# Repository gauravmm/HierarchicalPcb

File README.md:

This project is retired, and has been superseded by [ProjectInstances](https://github.com/OfficialDyray/ProjectInstances/). Please use that instead!

# ~HierarchicalPcb~

This provides a true hierarchical PCB layout engine in KiCad, mirroring its hierarchical schematic capabilities.

Instead of laying out everything in your final file, you can define a sub-PCB next to your sub-schematic file, and HierarchicalPCB will automatically force the sub-PCB to be laid out exactly like that in the final PCB. There's no depth limitation to the nesting -- in fact, we encourage organizing your PCB layouts for maximum reusability.

This is inspired by the venerable [`ReplicateLayout`](https://github.com/MitjaNemec/ReplicateLayout) plugin, and is intended to be a more modular, powerful, and flexible replacement.

**Installation**:

This requires KiCad 8 to run. For now, you have to manually download or clone this repository to the plugin directory. On Windows, this is `C:\Users\<Username>\Documents\KiCad\8.0\3rdparty\plugins`.

I'm working on getting this deployed to the official repository or on hosting my own.

## How To Use

In summary:

1. Organize your schematic into hierarchical sheets, as you would normally do.
2. Create a `.kicad_pcb` file next to a hierarchical sheet and set up the placement of the sub-PCB there.

   a. You should create a project file to help with the placement.
   b. Any footprints missing from the sub-PCB (but present in the schematic) will be ignored during automatic placement.
   c. Any footprints present in the sub-PCB but missing from the main PCB will be ignored.
   d. Any footprints placed off to the left or above the origin will be ignored during automatic placement.

3. Open the main PCB and run the plugin.
4. Select which hierarchical sheets you want to enforce the layout of, and configure which footprint to use as the anchor for each sub-PCB.
5. Click OK and watch the magic happen.

If you wish to see a project that uses this, check out [AngloDox, my keyboard project](https://github.com/gauravmm/AngloDox/). We use HierarchicalPCB to provide for rich per-key circuitry.

### In Detail

Begin by preparing your hierarchical schematic as per normal. In this example, we have a simple circuit for a single key in a keyboard, including an LED and an RC debouncing circuit:

This would be an absolute nightmare to layout ~90 different times; that's where HierarchicalPCB comes in: after creating the schematic inside the main project, we:

1. create a new project with the same name as the `sch` file,
2. open that project in KiCAD, taking care not to change the schematic while the main project is open
3. create a PCB inside the project,
4. update the PCB from the schematic,
5. layout the PCB for the schematic.

When complete, this should look like:

Great! Now we're ready to propagate this layout to every key on the main PCB. To do that, create a new PCB in the **main** project (i.e., at the root level), and lay out the "anchor" component in each. The anchor component is the component around which all other components will be moved into position and all traces will be drawn. Here we choose the switch (`SW???01`) to be the anchor component and lay it out in the shape of our keyboard:

This layout was done using my [KLEPlacement plugin](https://github.com/gauravmm/KLEPlacement) from this [KLE file](https://github.com/gauravmm/AngloDox/blob/master/keyboard-layout-left.json). Note that only the switch components are moved into position, all other components are unmoved.

To enforce our desired layout around each key we invoke the plugin. Click on the button in the top bar to start:

This opens up the menu where you configure the plugin. The window is split into two panes: the upper lets you pick which sub-schematics to enforce the layout for; the lower lets you pick the anchor for each sub-PCB you define. The plugin remembers the last selections you made (writing it to a file next to the `.pcb` file).

First, we select which sub-schematics to enforce the layout for. The plugin allows you to arbitrarily nest PCBs, so one sub-PCB can itself have sub-sub-PCBs, but at any one time the contents of each schematic may only be arranged according to one sub-PCB. You can select which sub-schematics to arrange by double-clicking each element. If you click "Reset to Default", it automatically selects the outermost PCB for each possible schematic.

Next, you select the anchor element for each PCB. You do this by clicking on the row and picking a new anchor in the drop-down box below.

Once you've done both, click "Apply" and watch the magic happen:

Ta-da!

And since the plugin remembers your settings you can propagate any change in just two clicks.

## Notes and Details

1. Each footprint may only be positioned following one sub-PCB. If you have a sub-PCB with its own sub-sub-PCBs, you can only enforce the layout of one of them. This is enforced during the  selection process.
2. If you want multiple variations of the same schematic, you can nest them (i.e. LayoutVariant includes LayoutCommon and nothing else, each has a different sub-PCB, and you can enforce the layout of either one).
3. Currently, it does not support Zones, but I'll happily add that if someone needs it. Open an issue if you're interested and have some time to help me test it.

### Details of the placement algorithm

The algorithm works as follows:

1. For each selected hierarchical sheet, find the sub-PCB file and load it.
2. Match the anchor footprint in the sub-PCB to the anchor footprint in the main PCB.
   a. Copy some properties of the anchor footprint from the sub-PCB to the main PCB. In particular, move it to the same layer as the anchor footprint.
   b. Move the anchor footprint in the main PCB into an automatically-named group (or create it if it doesn't exist).
3. For each footprint in the sub-PCB, find the corresponding footprint in the main PCB.
   a. Match the footprint by internal ID, not the reference designator.
   b. Copy some properties.
   c. Place and rotate the main footprint w.r.t. the main anchor so that it matches the sub-PCB.
4. For all traces in the sub-PCB:
   a. Clear the traces in the main PCB in the same group as the anchor.
   b. Recreate all traces, arcs, and vias.

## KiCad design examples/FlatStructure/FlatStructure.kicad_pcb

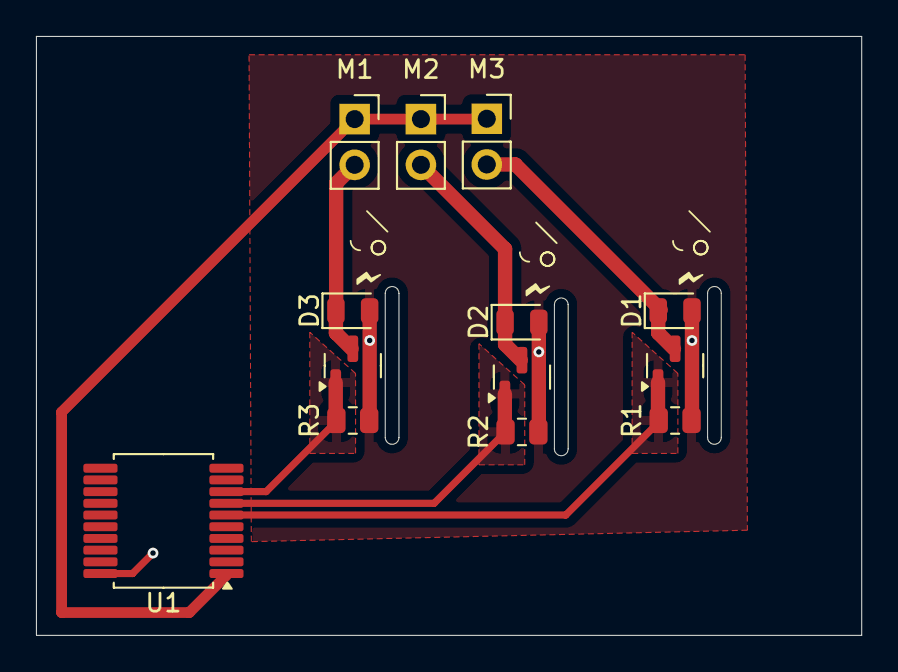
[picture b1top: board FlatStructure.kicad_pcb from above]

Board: 2 copper layers, 45.8 x 33.3 mm, 13 parts (0 on the bottom side), 8 nets.

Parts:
D1, D2, D3: D_Schottky_Small; D_0805_2012Metric
M1, M2, M3: Motor_DC; PinSocket_1x02_P2.54mm_Vertical
Q1, Q2, Q3: MMBT2222A; SOT-23
R1, R2, R3: 10k; R_0805_2012Metric
U1: ATtiny1626-X; SSOP-20_5.3x7.2mm_P0.65mm

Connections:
+3.3V: M1.1 (+), M2.1 (+), M3.1 (+), U1.1 (VCC)
/Sinking Digital1/Input: Q2.1 (B), R2.1, U1.7 (PB4)
/Sinking Digital1/Output: D2.1 (K), M2.2 (-), Q2.3 (C)
/Sinking Digital2/Input: Q3.1 (B), R3.1, U1.8 (PB3)
/Sinking Digital2/Output: D3.1 (K), M1.2 (-), Q3.3 (C)
/Sinking Digital/Input: Q1.1 (B), R1.1, U1.6 (PB5)
/Sinking Digital/Output: D1.1 (K), M3.2 (-), Q1.3 (C)
GND: D1.2 (A), D2.2 (A), D3.2 (A), Q1.2 (E), Q2.2 (E), Q3.2 (E), R1.2, R2.2, R3.2, U1.20 (GND)

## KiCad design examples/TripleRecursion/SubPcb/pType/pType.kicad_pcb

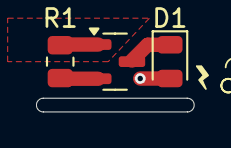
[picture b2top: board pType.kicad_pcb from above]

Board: 2 copper layers, 3 parts (0 on the bottom side), 3 nets.

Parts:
D1: D_Schottky_Small; D_0805_2012Metric
Q1: BC807; SOT-23
R1: 10k; R_0805_2012Metric

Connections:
/Input: Q1.1 (B), R1.2
/Output: D1.1 (K), Q1.3 (C)
VDC: Q1.2 (E), R1.1

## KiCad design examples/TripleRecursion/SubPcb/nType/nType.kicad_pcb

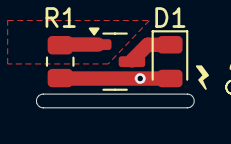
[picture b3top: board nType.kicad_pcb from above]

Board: 2 copper layers, 3 parts (0 on the bottom side), 3 nets.

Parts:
D1: D_Schottky_Small; D_0805_2012Metric
Q1: MMBT2222A; SOT-23
R1: 10k; R_0805_2012Metric

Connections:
/Input: Q1.1 (B), R1.1
/Output: D1.1 (K), Q1.3 (C)
GND: D1.2 (A), Q1.2 (E), R1.2

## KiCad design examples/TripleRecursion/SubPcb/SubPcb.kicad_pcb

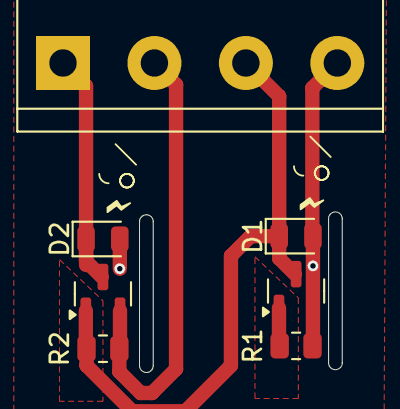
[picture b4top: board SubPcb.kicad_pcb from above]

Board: 2 copper layers, 7 parts (0 on the bottom side), 5 nets.

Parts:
D1, D2: D_Schottky_Small; D_0805_2012Metric
J1: Screw_Terminal_01x04; TerminalBlock_bornier-4_P5.08mm
Q1: MMBT2222A; SOT-23
Q2: BC807; SOT-23
R1, R2: 10k; R_0805_2012Metric

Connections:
/Input: Q1.1 (B), R1.1
/nType/Output: D1.1 (K), J1.3, Q1.3 (C), Q2.1 (B), R2.2
/pType/Output: D2.1 (K), J1.1, Q2.3 (C)
GND: D1.2 (A), D2.2 (A), J1.4, Q1.2 (E), R1.2
VDC: J1.2, Q2.2 (E), R2.1

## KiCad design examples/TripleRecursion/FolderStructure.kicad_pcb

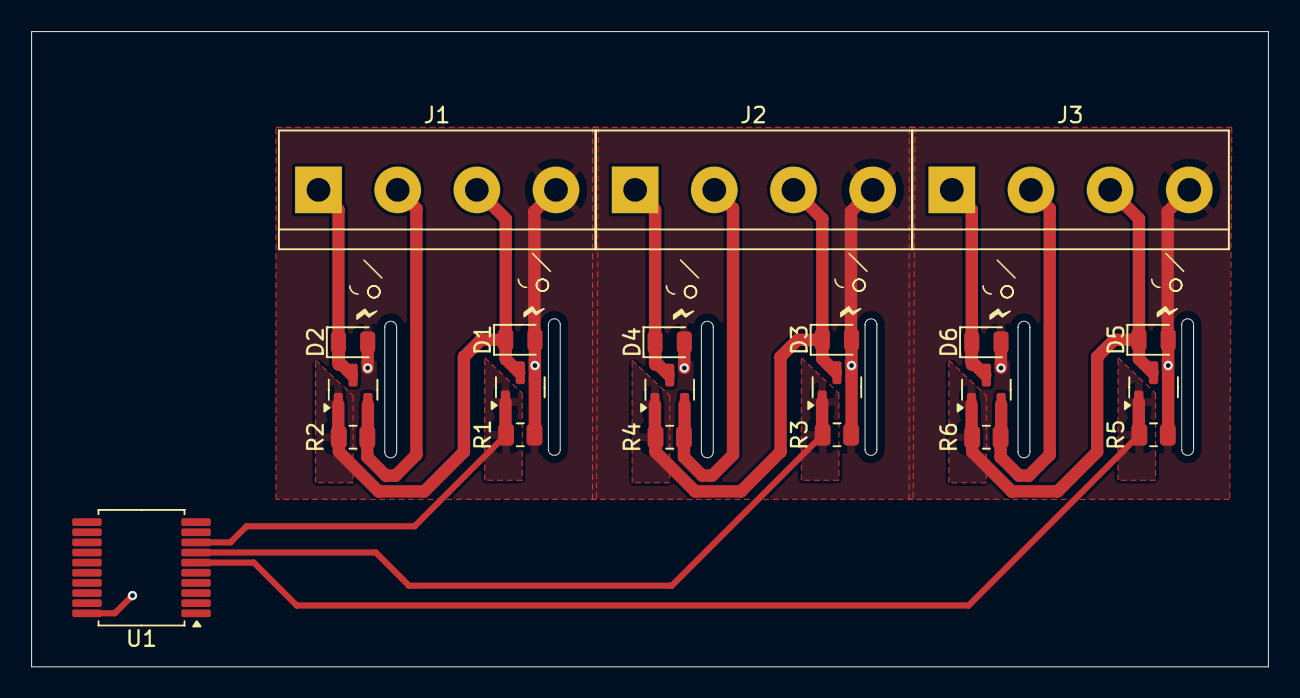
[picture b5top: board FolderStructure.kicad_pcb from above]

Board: 2 copper layers, 79.4 x 40.8 mm, 22 parts (0 on the bottom side), 11 nets.

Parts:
D1, D2, D3, D4, D5, D6: D_Schottky_Small; D_0805_2012Metric
J1, J2, J3: Screw_Terminal_01x04; TerminalBlock_bornier-4_P5.08mm
Q1, Q3, Q5: MMBT2222A; SOT-23
Q2, Q4, Q6: BC807; SOT-23
R1, R2, R3, R4, R5, R6: 10k; R_0805_2012Metric
U1: ATtiny1626-X; SSOP-20_5.3x7.2mm_P0.65mm

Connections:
/SubPcb1/Input: Q3.1 (B), R3.1, U1.7 (PB4)
/SubPcb1/nType/Output: D3.1 (K), J2.3, Q3.3 (C), Q4.1 (B), R4.2
/SubPcb1/pType/Output: D4.1 (K), J2.1, Q4.3 (C)
/SubPcb2/Input: Q5.1 (B), R5.1, U1.6 (PB5)
/SubPcb2/nType/Output: D5.1 (K), J3.3, Q5.3 (C), Q6.1 (B), R6.2
/SubPcb2/pType/Output: D6.1 (K), J3.1, Q6.3 (C)
/SubPcb/Input: Q1.1 (B), R1.1, U1.8 (PB3)
/SubPcb/nType/Output: D1.1 (K), J1.3, Q1.3 (C), Q2.1 (B), R2.2
/SubPcb/pType/Output: D2.1 (K), J1.1, Q2.3 (C)
GND: D1.2 (A), D2.2 (A), D3.2 (A), D4.2 (A), D5.2 (A), D6.2 (A), J1.4, J2.4, J3.4, Q1.2 (E), Q3.2 (E), Q5.2 (E), R1.2, R3.2, R5.2, U1.20 (GND)
VDC: J1.2, J2.2, J3.2, Q2.2 (E), Q4.2 (E), Q6.2 (E), R2.1, R4.1, R6.1

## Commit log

2023-07-30 Starting
2023-07-30 Still doesn't work
2023-07-30 We can read the hierarchical PCB
2023-07-31 Added dialog
2023-08-01 Figured out how to structure code.
2023-08-01 Populate UI
2023-08-02 Working on TreeView
2023-08-02 Working on UI highlighting
2023-08-02 About to abandon the current TreeListControl
2023-08-02 Switched to treeview.
2023-08-04 Populate and intelligent defaults.
2023-08-04 Added support for config manager.
2023-08-05 Working on UI and saving program state.
2023-08-05 Can't get it to play nice with nested Modals.
2023-08-05 Slowly working on getting the thing working.
2023-08-06 Load and save with better UI
2023-08-06 It works!
2023-08-09 Moving parts into the appropriate group.
2023-08-09 Abstracted the GroupManager
2023-08-12 Support for traces.
2023-08-12 Remove old traces each time.
2023-08-14 Remove main logging.
2023-09-02 Added documentation
2023-09-09 Installation notes.
2023-09-10 Moved the icon file.
2023-11-01 Fix Filled Area/Zone not copying
2023-11-02 Fix vias & zones not having the correct net
2023-11-02 Fix arc mid incorrect value
2023-11-03 Fix unknown nets being created
2023-11-19 Updated net getter with new name.
2023-11-19 Switched to walrus operator.
2024-01-13 Fix vias and arcs not showing up caused by class id mismatch
    causing isinstance to not match the track type and copy vias and arcs over as tracks, and prevents clear_traces to run too
2024-02-11 add via delete
2024-02-27 8.0 Update
2024-02-28 PCB_FIELD instead of PCB_TEXT
2024-03-04 Changed capitalization.
2024-03-21 fix: footprint text rotation if not similar to footprint rotation
2024-03-22 feat: use ✅ and ❌ instead of font weight change
2024-03-22 feat: sort items and improve labels
2024-03-22 feat: hide unusable sheets
2024-03-24 Folder Restructure
2024-03-24 Drawings Support
2024-03-24 PCB_field flip status
2024-03-25 Show First Schematic
2024-03-25 zoneFix
2024-03-28 Faster
2024-03-30 Root Correction
2024-03-30 Example Improvement
2024-04-06 Remove Recursion
2024-04-17 Small Via Fix
2024-05-05 Unpacked src directory. I prefer it this way for development.
2024-05-05 Updated the description.
2024-05-05 Finished up support for kicad 8
2024-05-16 Better Var names
2024-05-16 Fix Broken Zone Nets
2024-05-16 FpText Cloning
2024-05-17 Better Net Assign
2024-05-17 Add Zones to Examples
2025-05-06 Fix kicad 9 rename of [Get/Set]ZoneConnection to [Get/Set]LocalZoneConnection
2025-05-17 crash on field delete workaround
2025-12-11 Update placement.py
    Add ":" at the end of line 354 to close the if statement.
2026-01-18 Initial commit.
2026-01-24 Revise README to reflect project retirement
    Updated README to indicate project retirement and redirect to ProjectInstances.
